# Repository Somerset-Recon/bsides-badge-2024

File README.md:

# BSides Badge 2024
<div align="center">
<table>
  <tr>
    <td></td>
    <td></td>
  </tr>
  <tr>
    <td><em><center>Front</center></em></td>
    <td><em><center>Back</center></em></td>
  </tr>
  <tr>
 </table>
<table>
  <tr>
    <td></td>
  </tr>
  <tr>
    <td align=center><em>Flashed Badges</em></td>
  </tr>
  <tr>
 </table>
 </div>

This repository contains hardware and firmware information needed to create and/or modify the Bsides Conference 2024 badge. All Gerber files, kiCad schematics, and other hardware-related files can be found in the "kiCad" folder. Associated source code and required libraries can be found in the "software" folder. We welcome BSides CTF players to submit writeups. Badge related writeups will be populated below.

Disclaimer: Somerset Recon is not liable nor responsible for any and all forks, branches, and duplication of the badge hardware or software created by an entity other than Somerset Recon.

The Badge for the San Diego Bsides Conference is a game that involves wireless rock-paper-scissors. There are hidden hacking challenges accessible over UART with a Wargames movie theme. 400 badges were distributed at the BSides San Diego 2024 Conference.

## Gameplay

The object of the game was to score the most points. Points were earned by hacking other players. The badges have two states: Attack mode and defend mode. 

 	A red LED on a badge will indicate that the player is in attack mode. Players will click the scan button. During a scan, BLE on the baddge will search for devices that are advertising (devices in defend mode). Once a connection is established, the player will be notified to choose rock, paper or scissors. The attacker gains points for each second they are connected to a defender. Once the defender notices that they are being attacked, they will choose rock, paper, or scissors. 
## WOPR Interface
<div align="center">
<table>
  <tr>
    <td></td>
    <td></td>
  </tr>
  <tr>
    <td align=center><em>Global Thermonuclear War</em></td>
    <td align=center><em>Tic-Tac-Toe</em></td>
  </tr>
  <tr>
</table>
</div>
Various challenges in the form of WOPR games are accessible using UART over the SAO connector. Each challenge contains its own flag to earn points in the BSides CTF.

# Flashing Instructions
> [!NOTE]
> In the latest source code, a cool glitch-like display will appear for the custom name when "SCAN" is held at boot. The conference badges were flashed with earlier firmware and do not have this feature. To add this glitch-like display, the badge must be flashed with the latest source code.
## Materials
- Arduino IDE
- TAG Connector (6-pin without legs)
## Procedure
1. Copy the Ticker library in this repository to the arduino library folder. Do *not* download the Ticker library via the Library Manager.
2. Open the Arduino IDE.
3. Open the source code file "latest.ino". All files in the folder should be automatically added when loaded.
4. Navigate to Board Manager and download the "esp32" board by Espressif Systems.
5. Turn on the badge and connect the TAG Connector to the TAG port. Plug the TAG connect to your computer via USB.
6. Select the board "ESP32C3 Dev Module" and choose the port that the badge is connected to.
7. Press Upload. If the compilation fails, ensure you have all necessary libraries downloaded.

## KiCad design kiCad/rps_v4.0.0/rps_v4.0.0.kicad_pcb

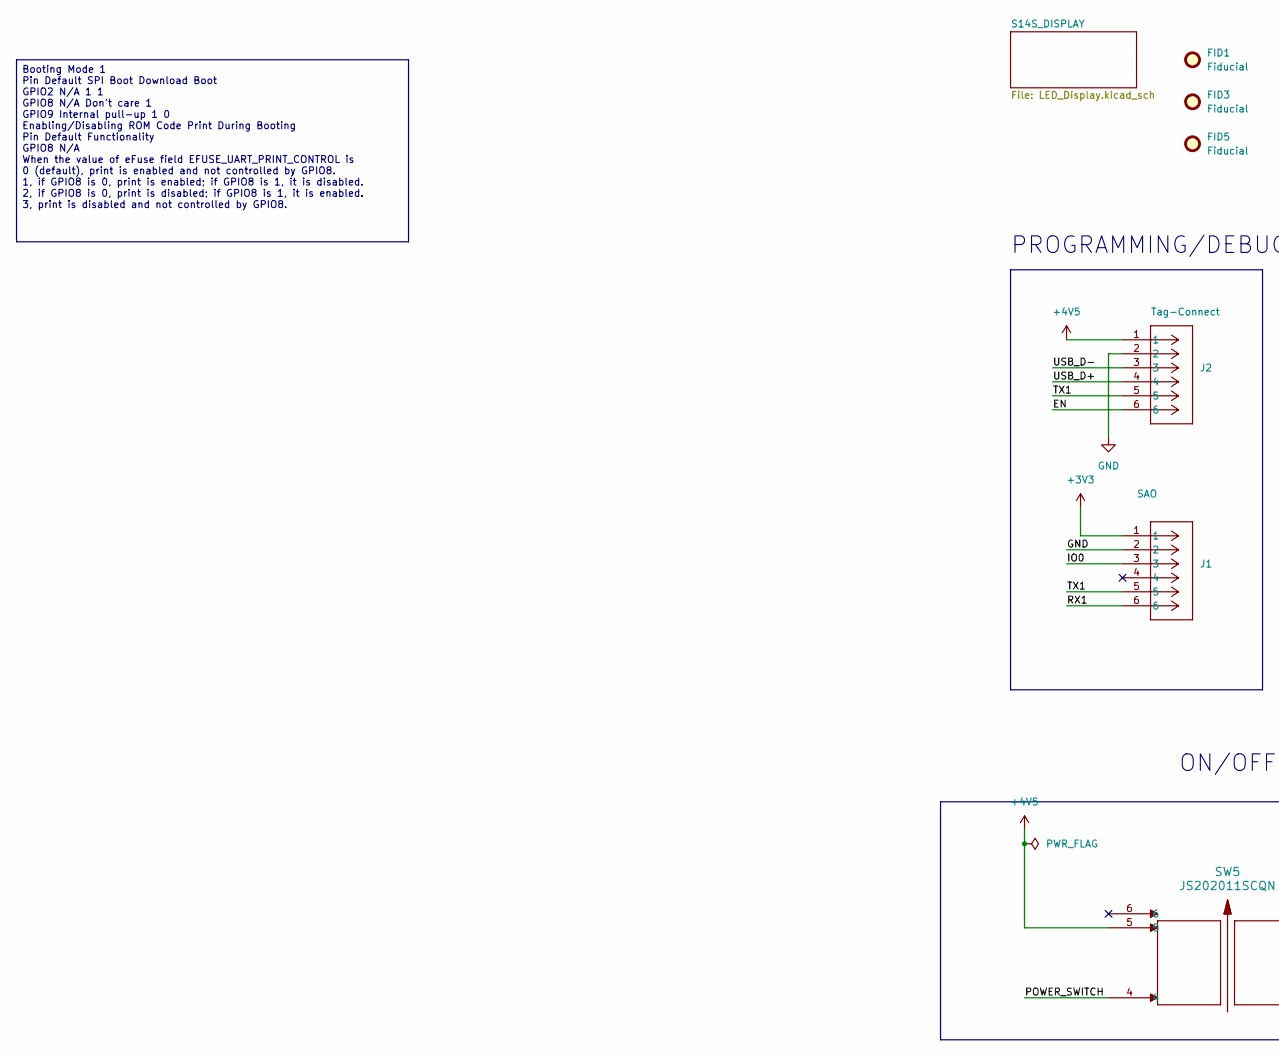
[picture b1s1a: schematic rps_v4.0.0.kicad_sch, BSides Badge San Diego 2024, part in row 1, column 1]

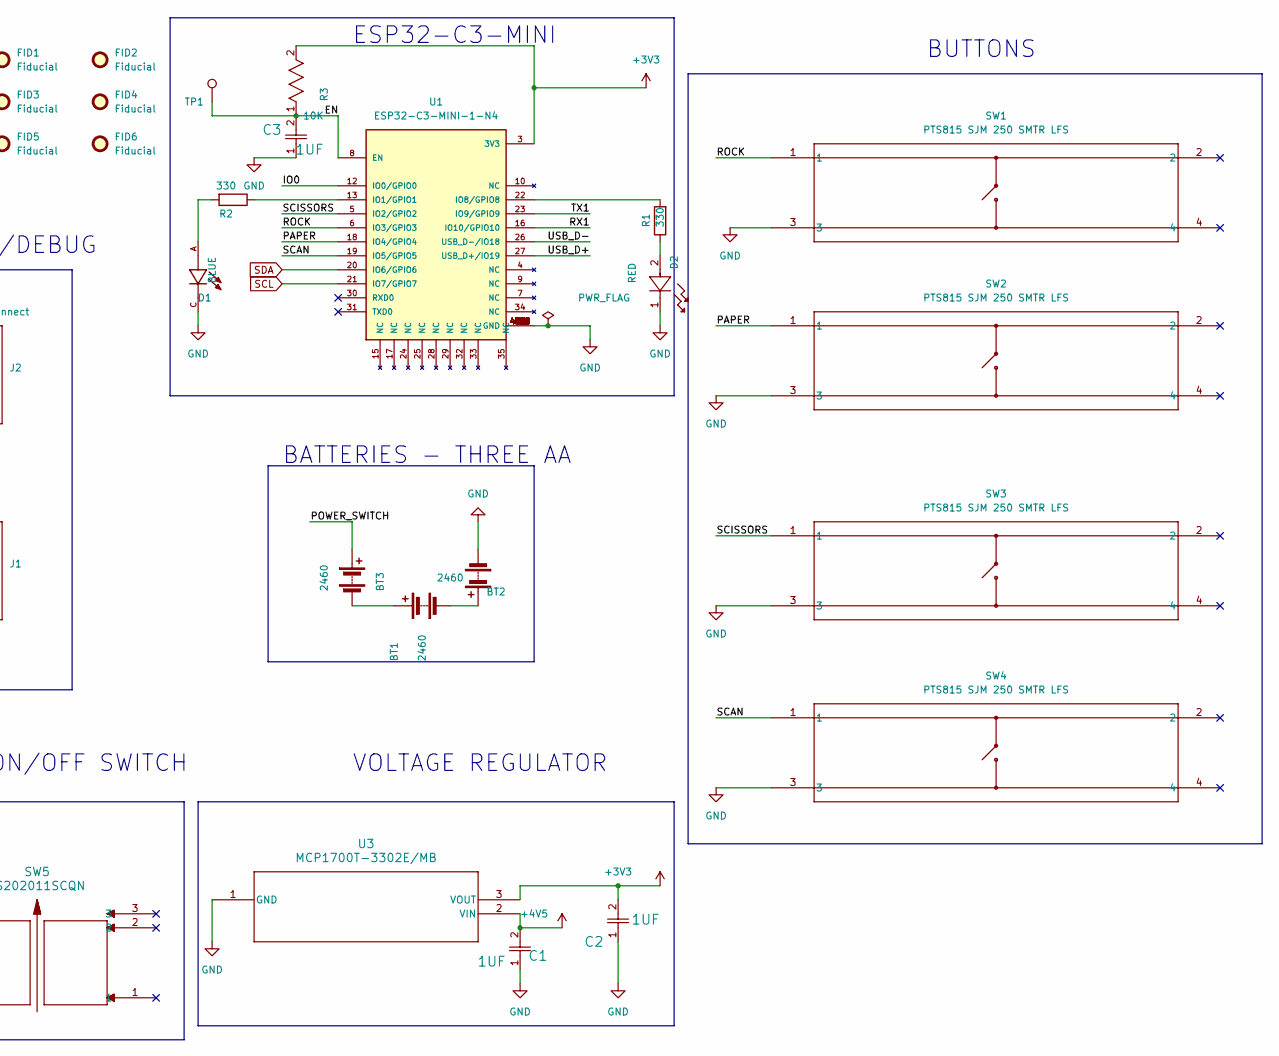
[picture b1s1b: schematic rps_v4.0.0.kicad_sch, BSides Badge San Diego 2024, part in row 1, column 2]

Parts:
BT1, BT2, BT3: 2460; BatteryHolder_Keystone_2460_1xAANO_HOLES
C1, C2, C3: 1UF; CAP_0603_1UF
D1: BLUE; LED_0805_BLUE
D2: RED; LED_0805_Red
FID1, FID2, FID3, FID4, FID5, FID6: Fiducial; Fiducial_0.75mm_Mask2.25mm
J1: SAO; SAO_CONN6_D03-ST-BK_SUL
J2: Tag-Connect; Tag-Connect_TC2030-IDC-NL_2x03_P1.27mm_Vertical
R1, R2: 330; R-0805
R3: 10K; RES_0805_10K
SW1, SW2, SW3, SW4: PTS815 SJM 250 SMTR LFS; PTS815_button
SW5: JS202011SCQN; ON_OFF_SW_JS202011SCQN
TP1: TestPoint; SolderWirePad_1x01_SMD_1x2mm
U1: ESP32-C3-MINI-1-N4; PARTREV v1.0
U3: MCP1700T-3302E/MB; MCP1700_LDO

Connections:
+3V3: C2.2, J1.1, R3.2, U1.3 (3V3), U3.3 (VOUT)
+4V5: C1.2, J2.1, SW5.5, U3.2 (VIN); also elsewhere on the board
/EN: C3.2, J2.6, R3.1, TP1.1, U1.8 (EN)
/IO0: J1.3, U1.12 (IO0/GPIO0)
/PAPER: SW2.1, U1.18 (IO4/GPIO4)
/POWER_SWITCH: BT3.1 (+), SW5.4
/ROCK: SW1.1, U1.6 (IO3/GPIO3)
/RX1: J1.6, U1.16 (IO10/GPIO10)
/SCAN: SW4.1, U1.19 (IO5/GPIO5)
/SCISSORS: SW3.1, U1.5 (IO2/GPIO2)
/TX1: J1.5, J2.5, U1.23 (IO9/GPIO9)
/USB_D+: J2.4, U1.27 (USB_D+/IO19)
/USB_D-: J2.3, U1.26 (USB_D-/IO18)
GND: BT2.2 (-), C1.1, C2.1, C3.1, D1.C, D2.1, J1.2, J2.2, SW1.3, SW2.3, SW3.3, SW4.3, U1.1 (GND), U1.2 (GND), U1.11 (GND), U1.14 (GND), U1.36 (GND), U1.37 (GND), U1.38 (GND), U1.39 (GND), U1.40 (GND), U1.41 (GND), U1.42 (GND), U1.43 (GND), U1.44 (GND), U1.45 (GND), U1.46 (GND), U1.47 (GND), U1.48 (GND), U1.49_1 (GND), U1.49_2 (GND), U1.49_3 (GND), U1.49_4 (GND), U1.49_5 (GND), U1.49_6 (GND), U1.49_7 (GND), U1.49_8 (GND), U1.49_9 (GND), U1.50 (GND), U1.51 (GND), U1.52 (GND), U1.53 (GND), U3.1 (GND); also elsewhere on the board
unnamed: BT1.1 (+), BT3.2 (-)
unnamed: BT1.2 (-), BT2.1 (+)
unnamed: D1.A, R2.2
unnamed: D2.2, R1.1
unnamed: R2.1, U1.13 (IO1/GPIO1)
unnamed: R1.2, U1.22 (IO8/GPIO8)
SCL: U1.21 (IO7/GPIO7); also elsewhere on the board
SDA: U1.20 (IO6/GPIO6); also elsewhere on the board

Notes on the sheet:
ESP32-C3-MINI
ON/OFF SWITCH
VOLTAGE REGULATOR
BUTTONS
BATTERIES - THREE AA
PROGRAMMING/DEBUG
Booting Mode 1 Pin Default SPI Boot Download Boot GPIO2 N/A 1 1 GPIO8 N/A Don't care 1 GPIO9 Internal pull-up 1 0 Enabling/Disabling ROM Code Print During Booting Pin Default Functionality GPIO8 N/A When the value of eFuse field EFUSE_UART_PRINT_CONTROL is 0 (default), print is enabled and not cont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

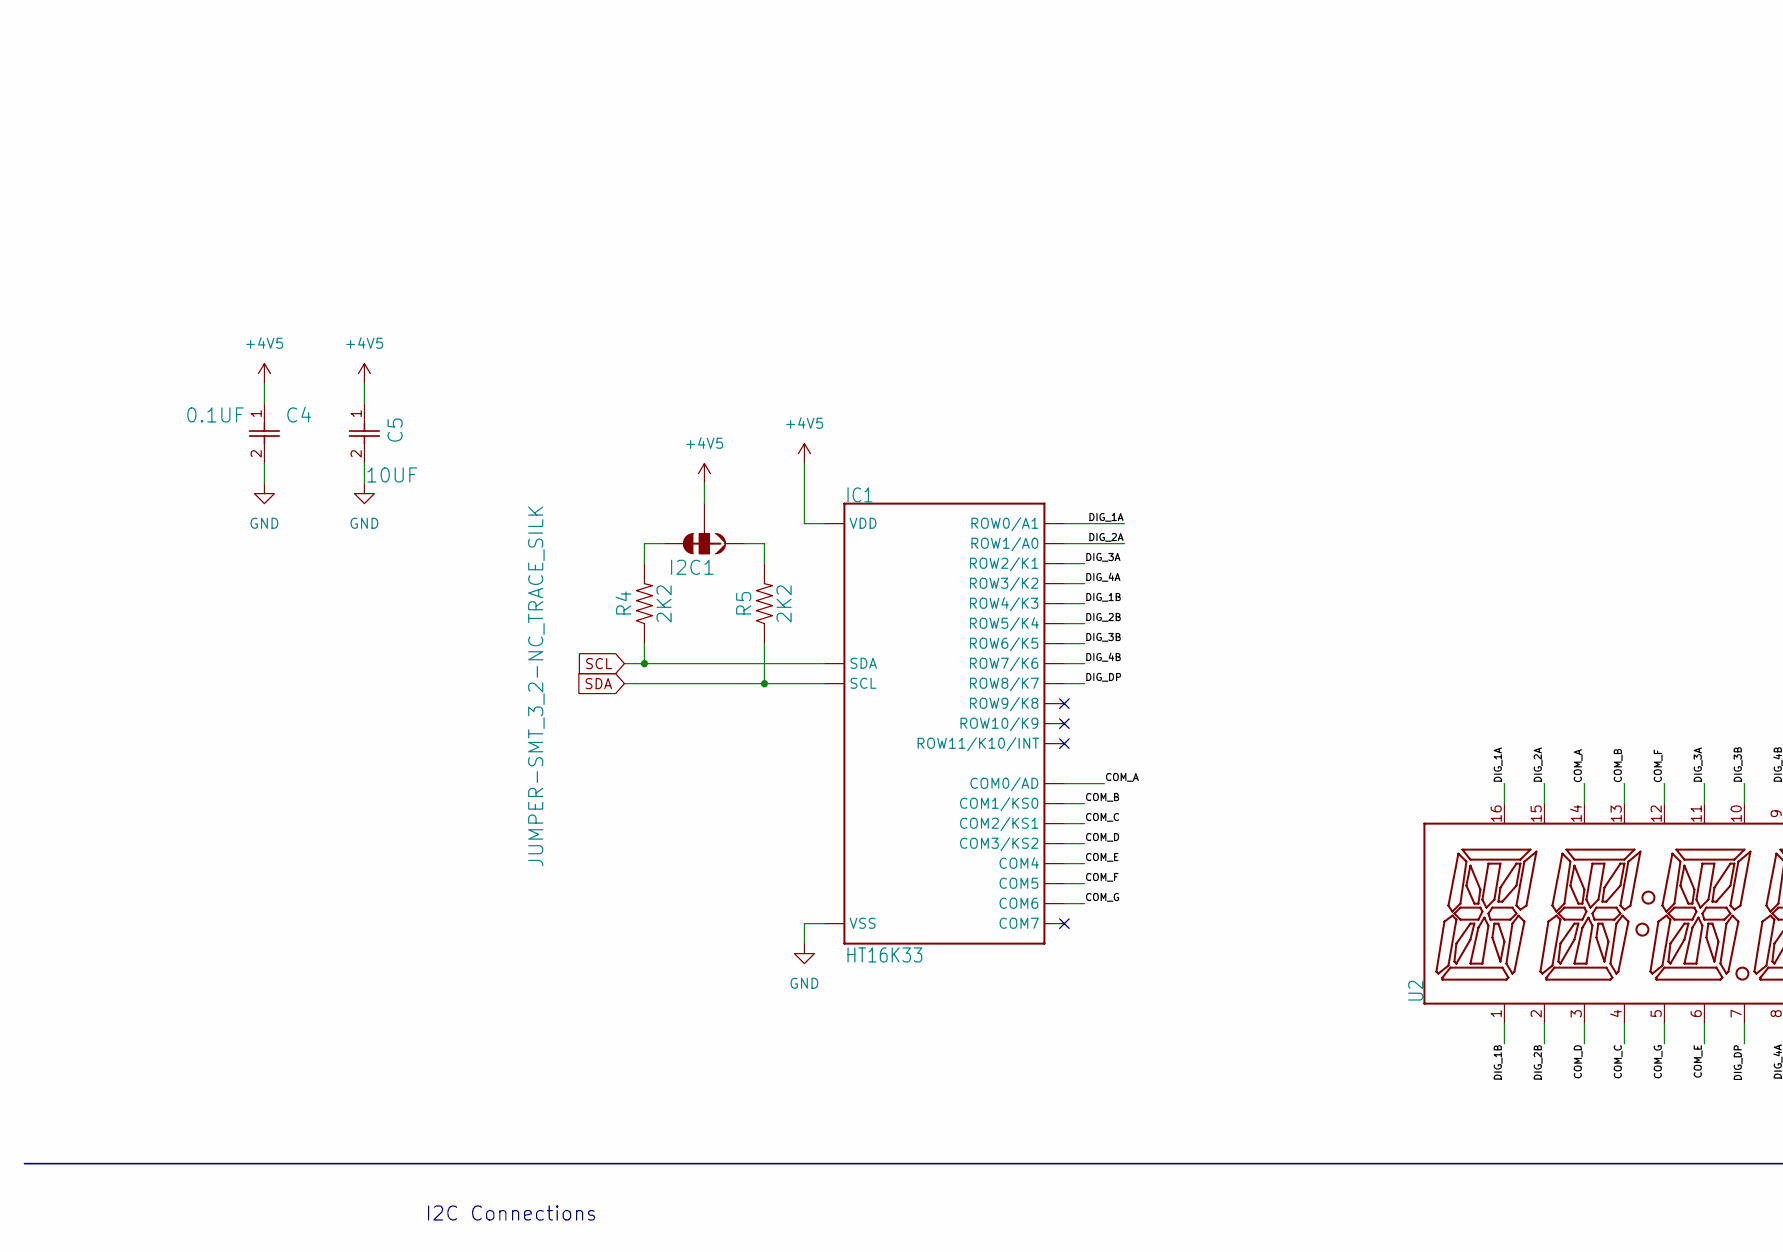
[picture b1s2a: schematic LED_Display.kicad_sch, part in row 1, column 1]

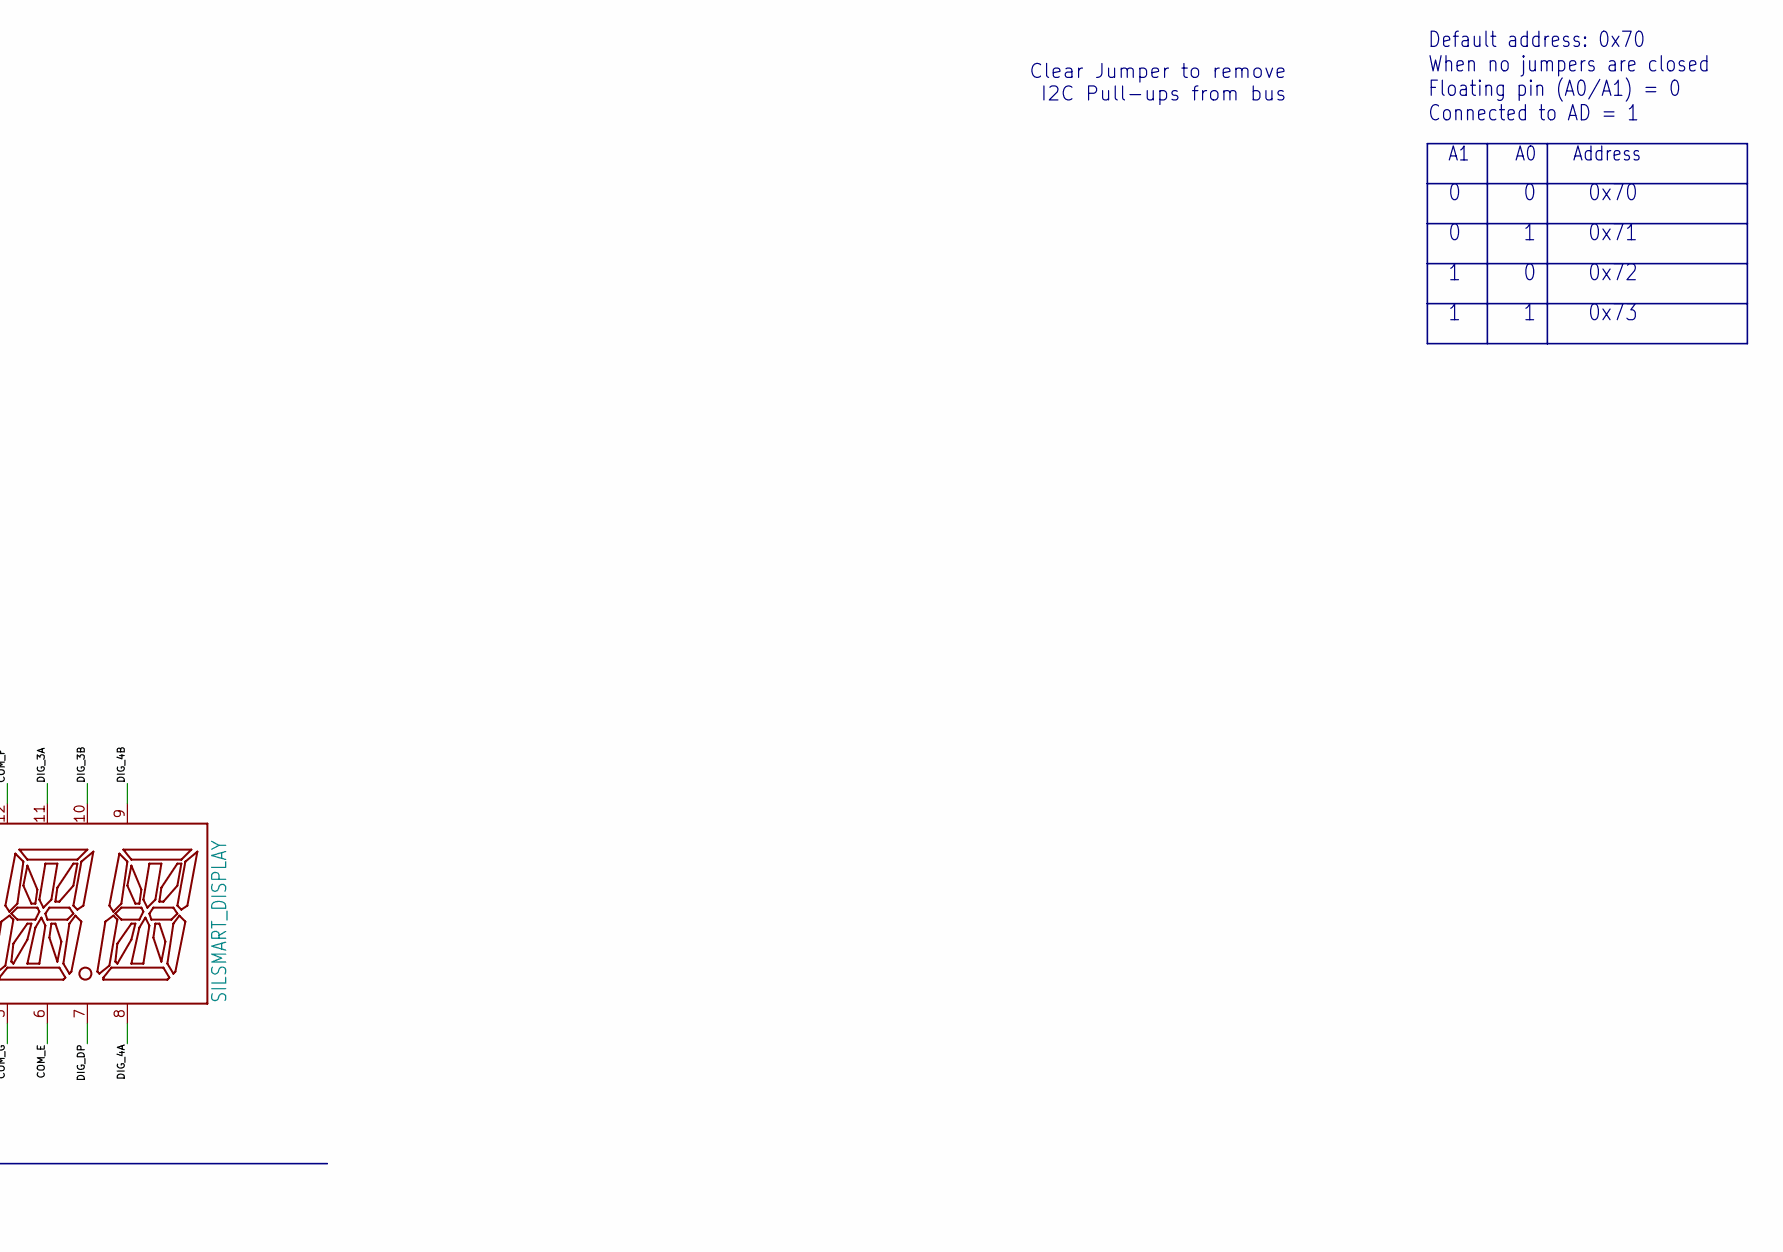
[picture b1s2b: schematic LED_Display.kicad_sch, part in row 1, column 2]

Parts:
C4: 0.1UF; CAP_0603_0.1UF
C5: 10UF; CAP_0603_10UF
I2C1: JUMPER-SMT_3_2-NC_TRACE_SILK; SMT-JUMPER_3_2-NC_TRACE_SILK
IC1: HT16K33; HT16K33A-24SOP
R4, R5: 2K2; 0603
U2: SILSMART_DISPLAY

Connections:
+4V5: C4.1, C5.1, I2C1.2, IC1.24 (VDD); also elsewhere on the board
/S14S_DISPLAY/COM_A: IC1.2 (COM0/AD), U2.14 (COM_A)
/S14S_DISPLAY/COM_B: IC1.3 (COM1/KS0), U2.13 (COM_B)
/S14S_DISPLAY/COM_C: IC1.4 (COM2/KS1), U2.4 (COM_C)
/S14S_DISPLAY/COM_D: IC1.5 (COM3/KS2), U2.3 (COM_D)
/S14S_DISPLAY/COM_E: IC1.6 (COM4), U2.6 (COM_E)
/S14S_DISPLAY/COM_F: IC1.7 (COM5), U2.12 (COM_F)
/S14S_DISPLAY/COM_G: IC1.8 (COM6), U2.5 (COM_G1)
/S14S_DISPLAY/DIG_1A: IC1.21 (ROW0/A1), U2.16 (DIG_1A)
/S14S_DISPLAY/DIG_1B: IC1.17 (ROW4/K3), U2.1 (DIG_1B)
/S14S_DISPLAY/DIG_2A: IC1.20 (ROW1/A0), U2.15 (DIG_2A)
/S14S_DISPLAY/DIG_2B: IC1.16 (ROW5/K4), U2.2 (DIG_2B)
/S14S_DISPLAY/DIG_3A: IC1.19 (ROW2/K1), U2.11 (DIG_3A)
/S14S_DISPLAY/DIG_3B: IC1.15 (ROW6/K5), U2.10 (DIG_3B)
/S14S_DISPLAY/DIG_4A: IC1.18 (ROW3/K2), U2.8 (DIG_4A)
/S14S_DISPLAY/DIG_4B: IC1.14 (ROW7/K6), U2.9 (DIG_4B)
/S14S_DISPLAY/DIG_DP: IC1.13 (ROW8/K7), U2.7 (DIG_DP)
GND: C4.2, C5.2, IC1.1 (VSS); also elsewhere on the board
unnamed: I2C1.1, R5.2
unnamed: I2C1.3, R4.2
SCL: IC1.23 (SDA), R4.1; also elsewhere on the board
SDA: IC1.22 (SCL), R5.1; also elsewhere on the board

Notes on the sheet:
Default address: 0x70 When no jumpers are closed Floating pin (A0/A1) = 0 Connected to AD = 1
Clear Jumper to remove I2C Pull-ups from bus
1 1 0x73
0 1 0x71
0 0 0x70
1 0 0x72
I2C Connections
A1 A0 Address

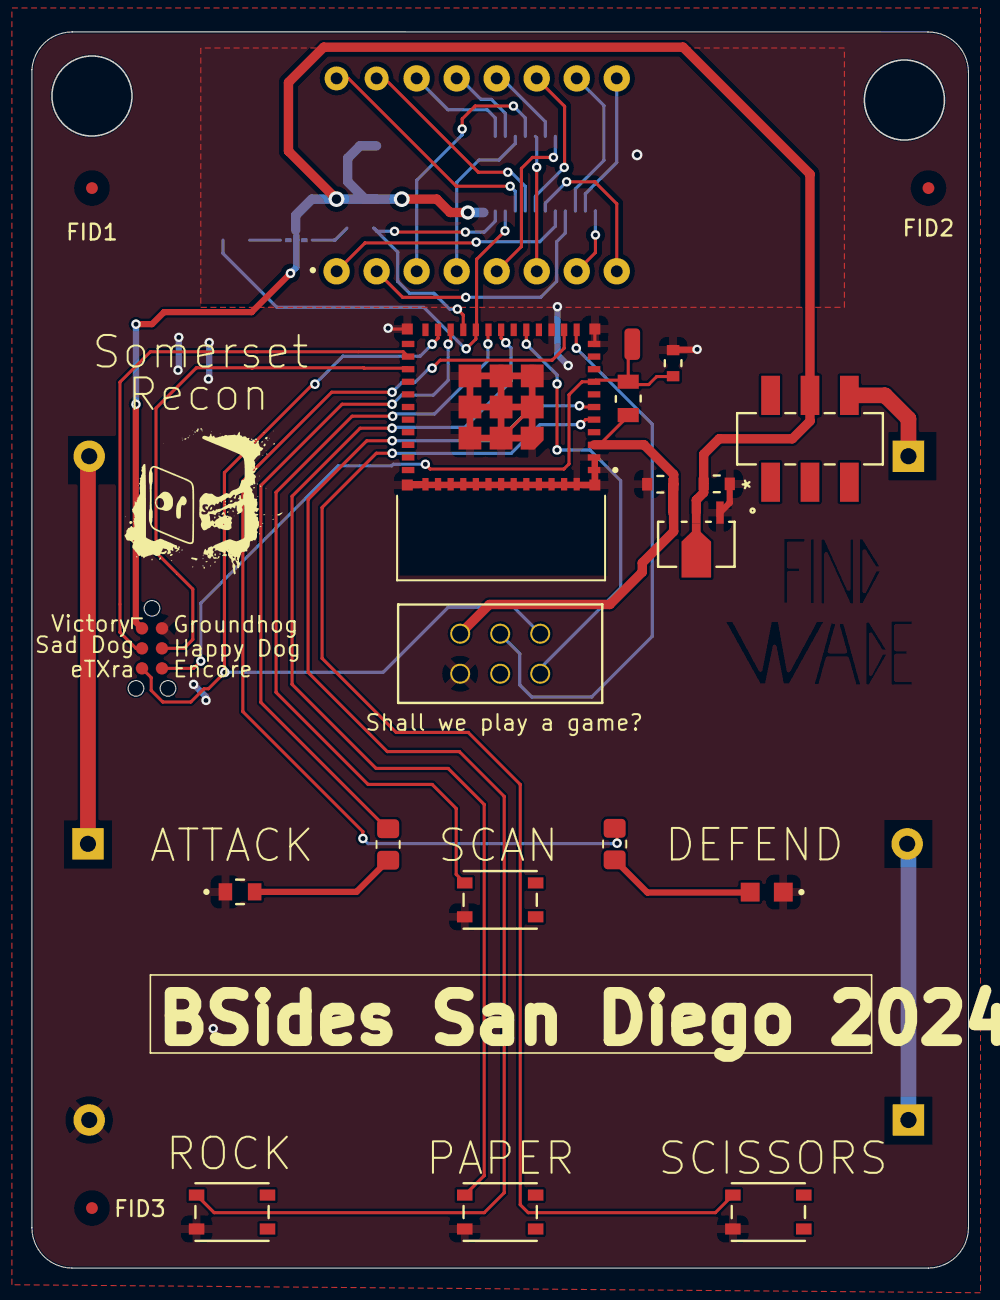
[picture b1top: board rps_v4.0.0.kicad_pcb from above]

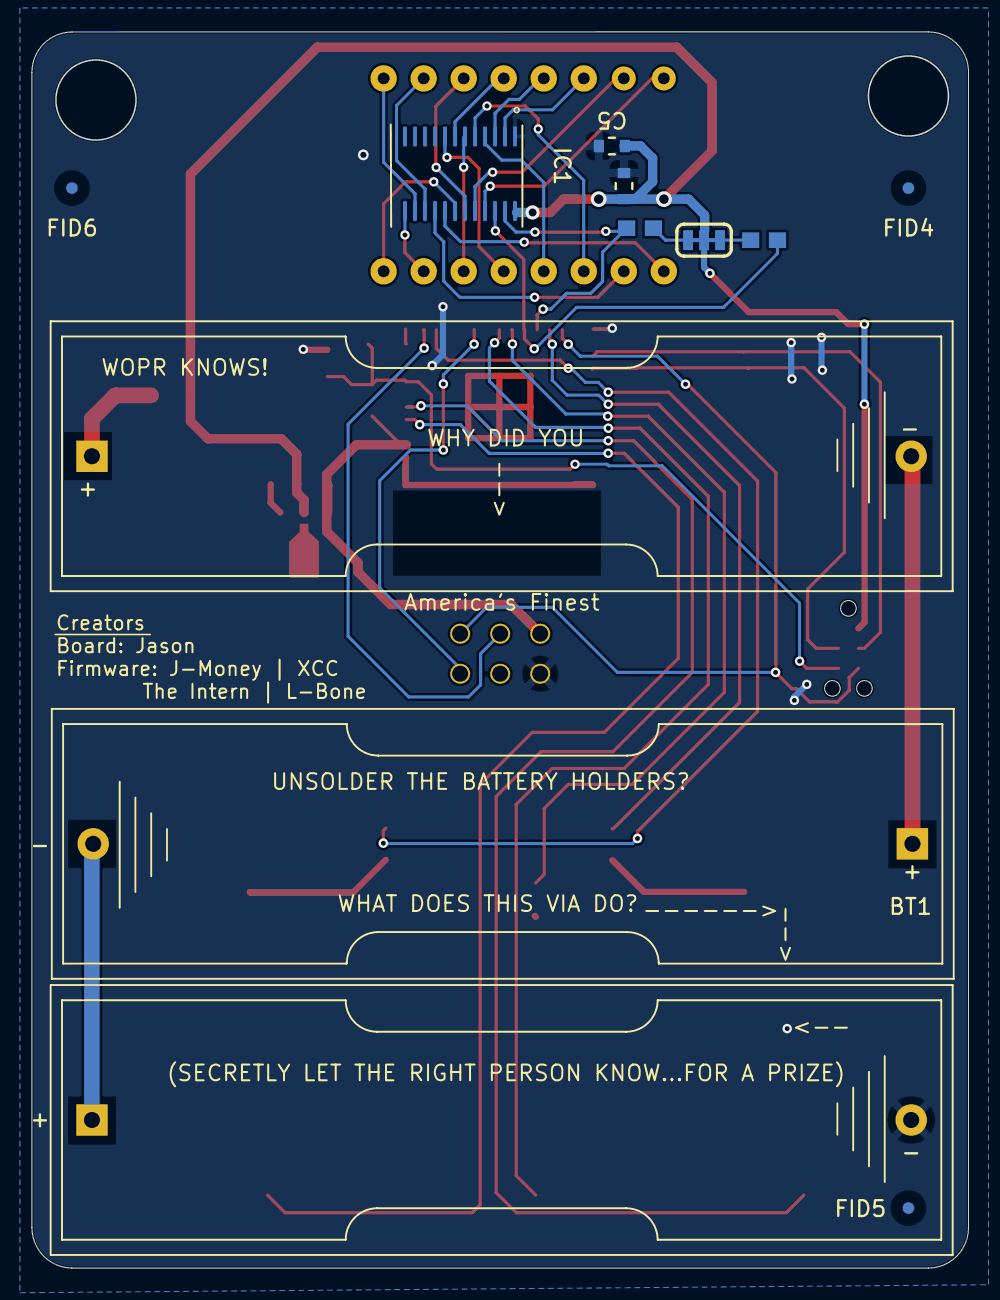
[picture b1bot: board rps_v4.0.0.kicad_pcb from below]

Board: 2 copper layers, 59.4 x 78.4 mm, 34 parts (12 on the bottom side), 40 nets.

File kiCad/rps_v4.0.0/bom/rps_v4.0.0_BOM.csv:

"Id";"Designator";"Footprint";"Quantity";"Designation";"Supplier and ref";
1;"BT1,BT2,BT3";"BatteryHolder_Keystone_2460_1xAANO_HOLES";3;"2460";;;
2;"R2,R1";"R-0805";2;"330";;;
3;"D2";"LED_0805_Red";1;"RED";;;
4;"U2";"SILSMART_DISPLAY";1;"SILSMART_DISPLAY";;;
5;"SW5";"ON_OFF_SW_JS202011SCQN";1;"JS202011SCQN";;;
6;"SW1,SW2,SW3,SW4";"PTS815_button";4;"PTS815 SJM 250 SMTR LFS";;;
7;"FID3,FID2,FID1,FID5,FID6,FID4";"Fiducial_0.75mm_Mask2.25mm";6;"Fiducial";;;
8;"C2,C3,C1";"CAP_0603_1UF";3;"1UF";;;
9;"R3";"RES_0805_10K";1;"10K";;;
10;"D1";"LED_0805_BLUE";1;"BLUE";;;
11;"J1";"SAO_CONN6_D03-ST-BK_SUL";1;"SAO";;;
12;"U1";"ESP32-C3-MINI-1-N4";1;"ESP32-C3-MINI-1-N4";;;
13;"U3";"MCP1700_LDO";1;"MCP1700T-3302E/MB";;;
14;"TP1";"SolderWirePad_1x01_SMD_1x2mm";1;"TestPoint";;;
15;"IC1";"HT16K33A-24SOP";1;"HT16K33";;;
16;"R5,R4";"0603";2;"2K2";;;
17;"C5";"CAP_0603_10UF";1;"10UF";;;
18;"C4";"CAP_0603_0.1UF";1;"0.1UF";;;

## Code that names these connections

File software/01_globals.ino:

#define SCAN 5
#define PAPER 4
#define ROCK 3
#define SCISSORS 2
#define UP SCAN
#define DOWN PAPER
#define LEFT ROCK
#define RIGHT SCISSORS
#define INT32_MAX 2147483647

#include <HardwareSerial.h>
HardwareSerial SerialSAO(1);

#include <WString.h>

bool exitState = false;
bool authenticated = false;


const byte numChars = 32;
char receivedChars[numChars];
bool newData = false;

const String flag = "FLAG{D3C0MP1L3_W1Z@RD}"; //requires dumping firmware to read

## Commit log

2024-04-26 remove latest folder
2024-06-18 Ticker library
